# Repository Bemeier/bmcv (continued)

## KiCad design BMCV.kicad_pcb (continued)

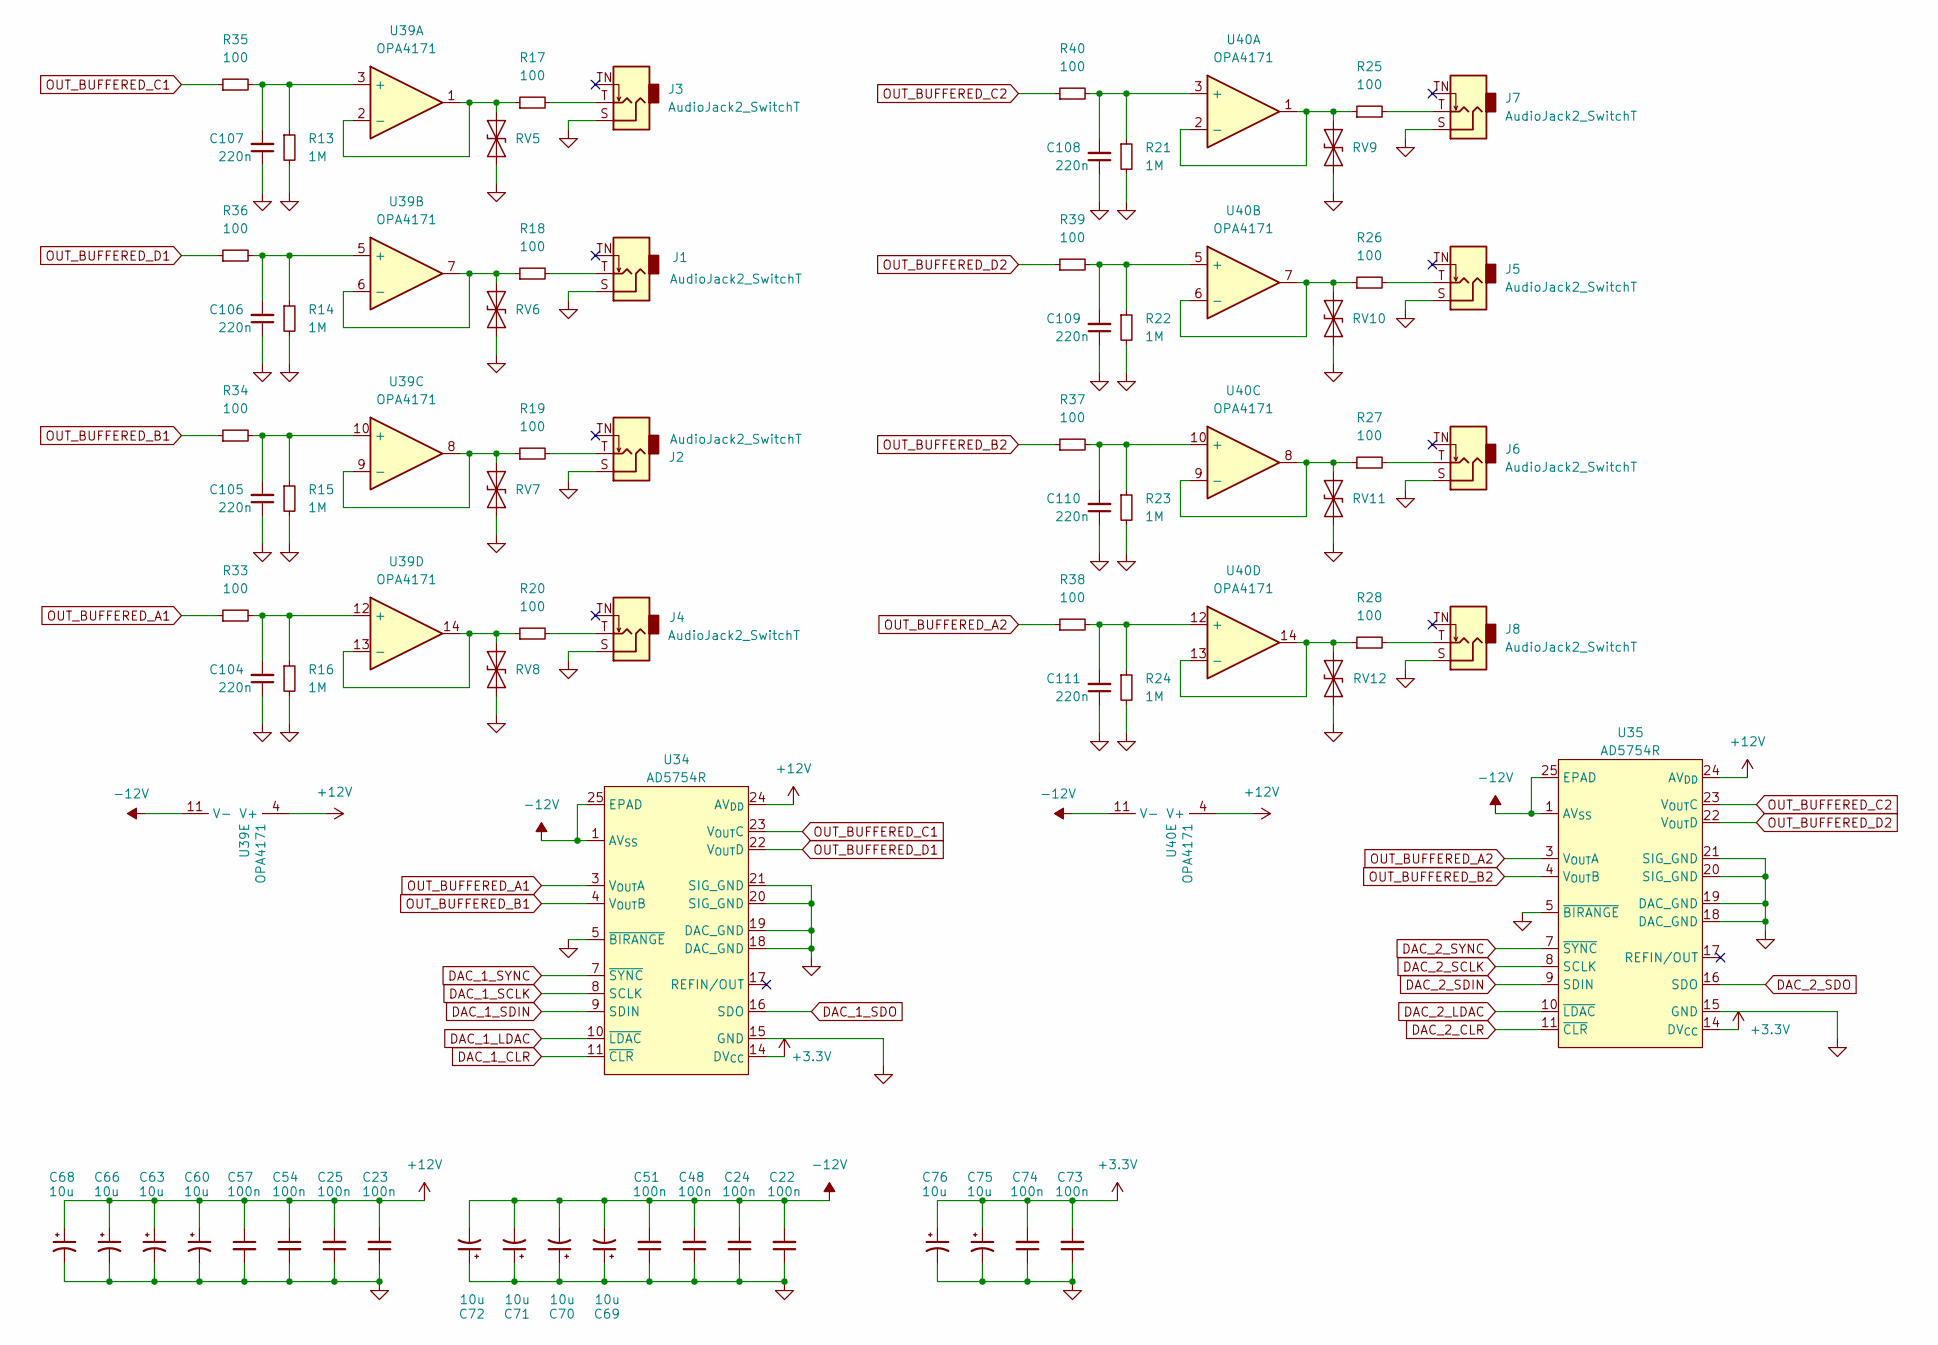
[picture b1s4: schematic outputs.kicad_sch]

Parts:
C22, C23, C24, C25, C48, C51, C54, C57, C73, C74: 100n; C_0603_1608Metric; LCSC Part # C14663
C60, C63, C66, C68, C69, C70, C71, C72, C75, C76: 10u; C_0805_2012Metric; LCSC Part # C237493
C104, C105, C106, C107, C108, C109, C110, C111: 220n; C_0402_1005Metric; LCSC Part # C16772
J1, J2, J3, J4, J5, J6, J7, J8: AudioJack2_SwitchT; Jack_3.5mm_QingPu_WQP-PJ398SM_Vertical_CircularHoles
R13, R14, R15, R16, R21, R22, R23, R24: 1M; R_0603_1608Metric; LCSC Part # C22935
R17, R18, R19, R20, R25, R26, R27, R28: 100; R_0603_1608Metric; LCSC Part # C22775
R33, R34, R35, R36, R37, R38, R39, R40: 100; R_0402_1005Metric; LCSC Part # C25076
RV5, RV6, RV7, RV8, RV9, RV10, RV11, RV12: SD12C-01FTG; D_SOD-323; LCSC Part # C135970
U34, U35: AD5754R; TSSOP-24-1EP_4.4x7.8mm_P0.65mm_EP3.2x5mm; LCSC Part # C392906
U39, U40: OPA4171; TSSOP-14_4.4x5mm_P0.65mm; LCSC Part # C529553

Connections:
3.3V: C73.2, C74.2, C75.1, C76.1, U34.10 (~LDAC), U34.11 (~CLR), U34.14 (DV_{CC}), U35.10 (~LDAC), U35.11 (~CLR), U35.14 (DV_{CC}); also elsewhere on the board
+12V: C23.2, C25.2, C54.1, C57.1, C60.1, C63.1, C66.1, C68.1, U34.24 (AV_{DD}), U35.24 (AV_{DD}), U39.4 (V+), U40.4 (V+); also elsewhere on the board
-12V: C22.2, C24.2, C48.2, C51.2, C69.2, C70.2, C71.2, C72.2, U34.1 (AV_{SS}), U34.25 (EPAD), U35.1 (AV_{SS}), U35.25 (EPAD), U39.11 (V-), U40.11 (V-); also elsewhere on the board
ADC_DAC_SCLK: U34.8 (SCLK), U35.8 (SCLK); also elsewhere on the board
ADC_DAC_SDIN: U34.9 (SDIN); also elsewhere on the board
DAC_1_SYNC: U34.7 (~SYNC), U35.7 (~SYNC); also elsewhere on the board
DAC_2_SDO: U35.16 (SDO)
GND: C22.1, C23.1, C24.1, C25.1, C48.1, C51.1, C54.2, C57.2, C60.2, C63.2, C66.2, C68.2, C69.1, C70.1, C71.1, C72.1, C73.1, C74.1, C75.2, C76.2, C104.1, C105.1, C106.1, C107.1, C108.1, C109.1, C110.1, C111.1, J1.S, J2.S, J3.S, J4.S, J5.S, J6.S, J7.S, J8.S, R13.2, R14.2, R15.2, R16.2, R21.2, R22.2, R23.2, R24.2, RV5.1 (A1), RV6.1 (A1), RV7.1 (A1), RV8.1 (A1), RV9.1 (A1), RV10.1 (A1), RV11.1 (A1), RV12.1 (A1), U34.5 (~BIRANGE), U34.15 (GND), U34.18 (DAC_GND), U34.19 (DAC_GND), U34.20 (SIG_GND), U34.21 (SIG_GND), U35.5 (~BIRANGE), U35.15 (GND), U35.18 (DAC_GND), U35.19 (DAC_GND), U35.20 (SIG_GND), U35.21 (SIG_GND); also elsewhere on the board
unnamed: J1.T, R18.2
unnamed: J2.T, R19.2
unnamed: J3.T, R17.2
unnamed: J4.T, R20.2
unnamed: J5.T, R26.2
unnamed: J6.T, R27.2
unnamed: J7.T, R25.2
unnamed: J8.T, R28.2
unnamed: R17.1, RV5.2 (A2), U39.1, U39.2 (-)
unnamed: R18.1, RV6.2 (A2), U39.6 (-), U39.7
unnamed: R19.1, RV7.2 (A2), U39.8, U39.9 (-)
unnamed: R20.1, RV8.2 (A2), U39.13 (-), U39.14
unnamed: R25.1, RV9.2 (A2), U40.1, U40.2 (-)
unnamed: R26.1, RV10.2 (A2), U40.6 (-), U40.7
unnamed: R27.1, RV11.2 (A2), U40.8, U40.9 (-)
unnamed: R28.1, RV12.2 (A2), U40.13 (-), U40.14
unnamed: C107.2, R13.1, R35.2, U39.3 (+)
unnamed: C106.2, R14.1, R36.2, U39.5 (+)
unnamed: C105.2, R15.1, R34.2, U39.10 (+)
unnamed: C104.2, R16.1, R33.2, U39.12 (+)
unnamed: C108.2, R21.1, R40.2, U40.3 (+)
unnamed: C109.2, R22.1, R39.2, U40.5 (+)
unnamed: C110.2, R23.1, R37.2, U40.10 (+)
unnamed: C111.2, R24.1, R38.2, U40.12 (+)
OUT_BUFFERED_A1: R33.1, U34.3 (V_{OUT}A)
OUT_BUFFERED_A2: R38.1, U35.3 (V_{OUT}A)
OUT_BUFFERED_B1: R34.1, U34.4 (V_{OUT}B)
OUT_BUFFERED_B2: R37.1, U35.4 (V_{OUT}B)
OUT_BUFFERED_C1: R35.1, U34.23 (V_{OUT}C)
OUT_BUFFERED_C2: R40.1, U35.23 (V_{OUT}C)
OUT_BUFFERED_D1: R36.1, U34.22 (V_{OUT}D)
OUT_BUFFERED_D2: R39.1, U35.22 (V_{OUT}D)

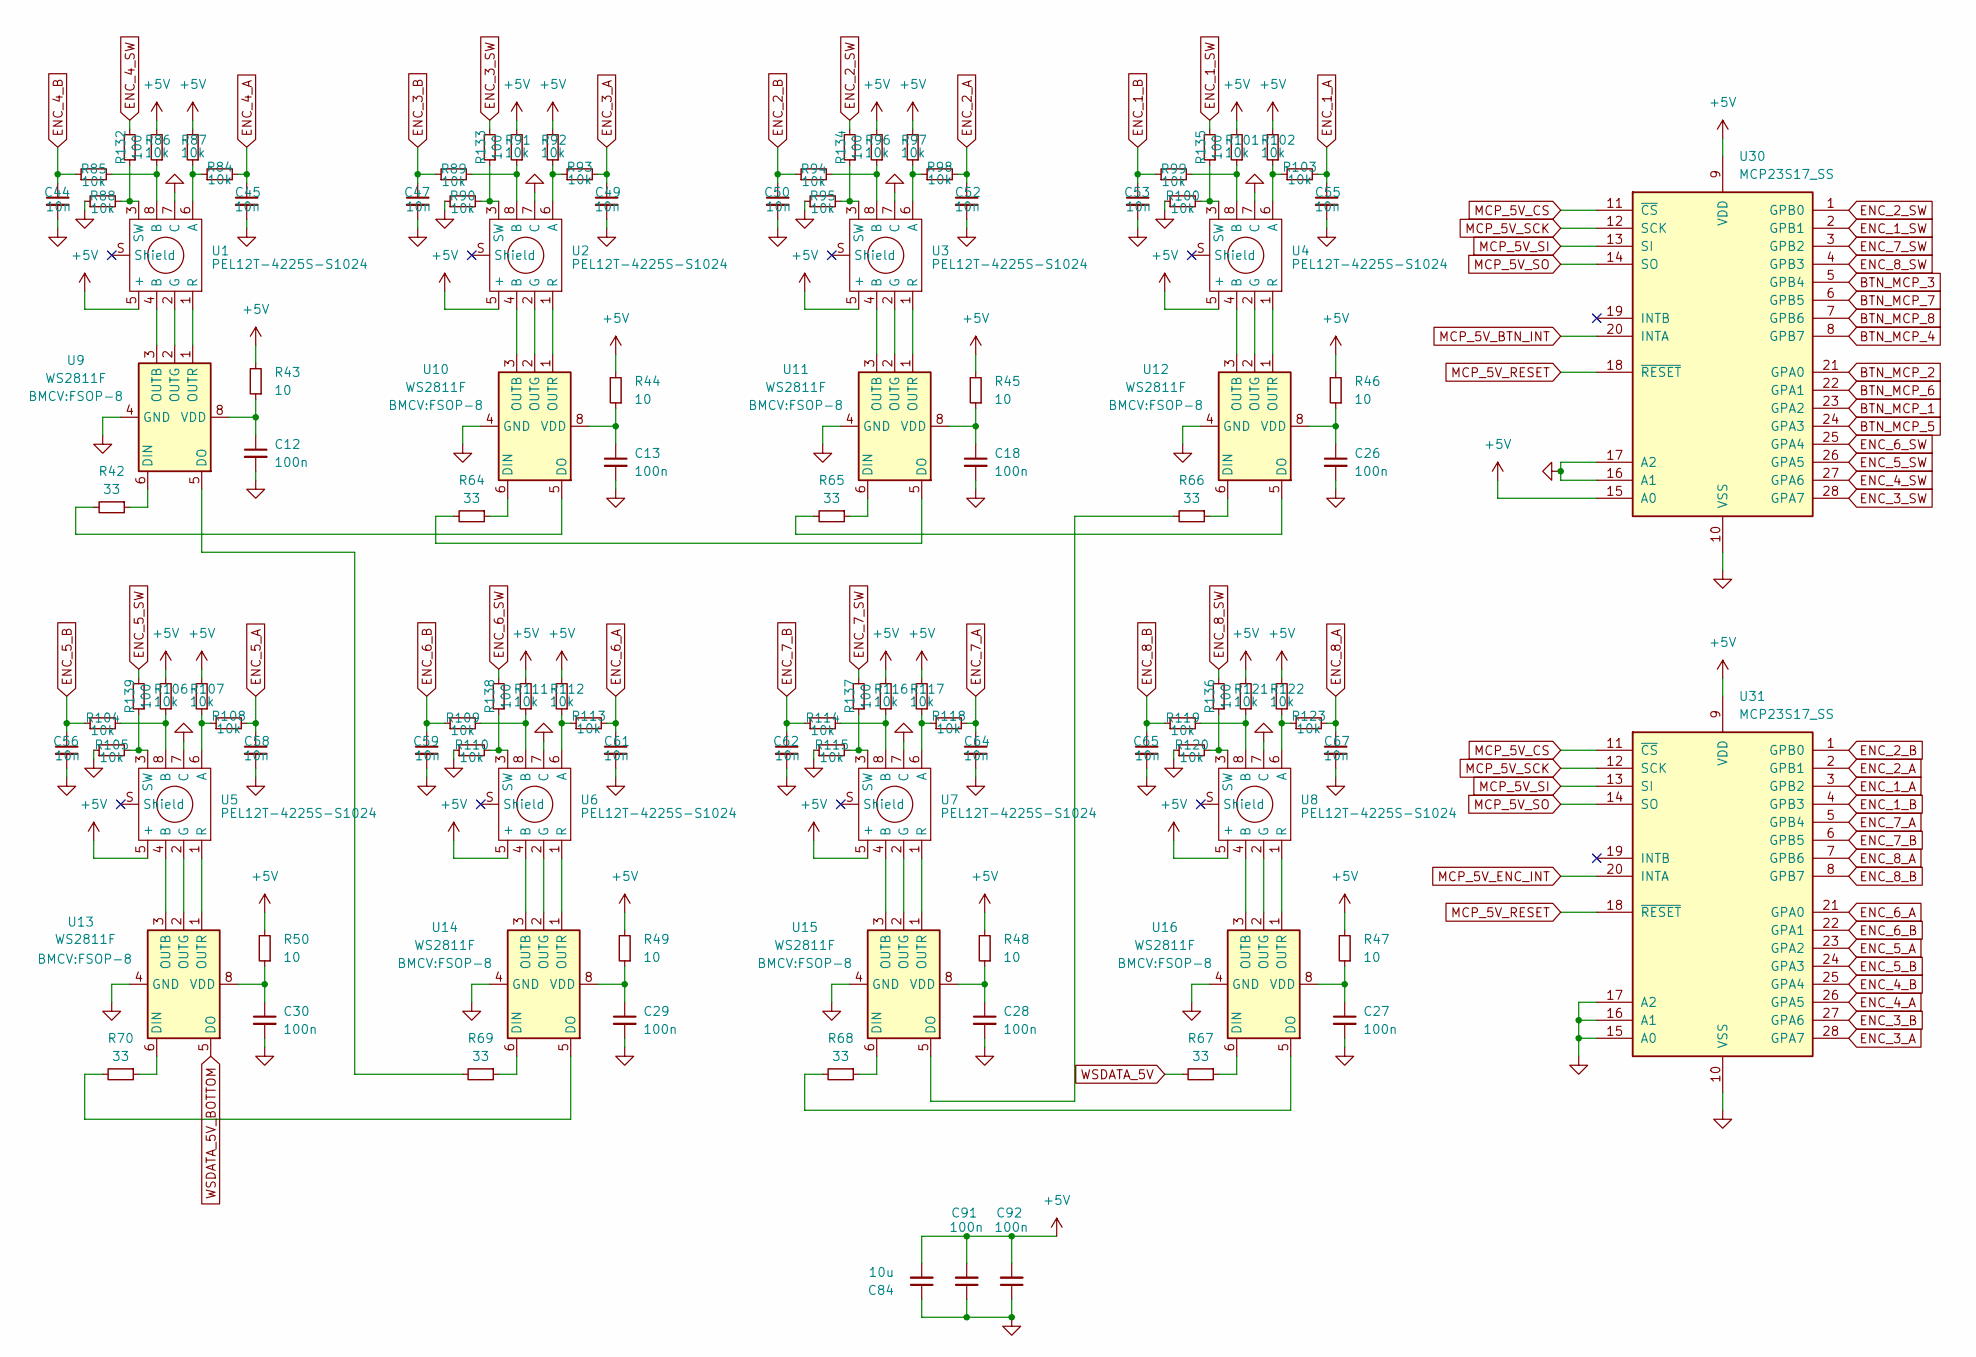
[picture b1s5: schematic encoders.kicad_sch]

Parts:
C12, C13, C18, C26, C27, C28, C29, C30: 100n; C_0402_1005Metric; LCSC Part # C307331
C44, C45, C47, C49, C50, C52, C53, C55, C56, C58, C59, C61, C62, C64, C65, C67: 10n; C_0402_1005Metric; LCSC Part # C15195
C84: 10u; C_0805_2012Metric; LCSC Part # C237493
C91, C92: 100n; C_0603_1608Metric; LCSC Part # C14663
R42, R64, R65, R66, R67, R68, R69, R70: 33; R_0402_1005Metric; LCSC Part # C25105
R43, R44, R45, R46, R47, R48, R49, R50: 10; R_0402_1005Metric; LCSC Part # C25077
R84, R85, R86, R87, R88, R89, R90, R91, R92, R93, R94, R95, R96, R97, R98, R99, R100, R101, R102, R103, R104, R105, R106, R107, R108, R109, R110, R111, R112, R113, R114, R115, R116, R117, R118, R119, R120, R121, R122, R123: 10k; R_0402_1005Metric; LCSC Part # C25744
R132, R133, R134, R135, R136, R137, R138, R139: 100; R_0402_1005Metric; LCSC Part # C25076
U1, U2, U3, U4, U5, U6, U7, U8: PEL12T-4225S-S1024; PEL12T-4xxxS-S1024
U9, U10, U11, U12, U13, U14, U15, U16: WS2811F; FSOP-8; LCSC Part # C5446692
U30, U31: MCP23S17_SS; SSOP-28_5.3x10.2mm_P0.65mm; LCSC Part # C128577

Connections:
+5V: C84.2, C91.2, C92.2, R43.2, R44.2, R45.2, R46.2, R47.2, R48.2, R49.2, R50.2, R86.2, R87.2, R91.2, R92.2, R96.2, R97.2, R101.2, R102.2, R106.2, R107.2, R111.2, R112.2, R116.2, R117.2, R121.2, R122.2, U1.5 (+), U2.5 (+), U3.5 (+), U4.5 (+), U5.5 (+), U6.5 (+), U7.5 (+), U8.5 (+), U30.9 (VDD), U30.15 (A0), U31.9 (VDD); also elsewhere on the board
BTN_MCP_1: U30.23 (GPA2); also elsewhere on the board
BTN_MCP_2: U30.21 (GPA0); also elsewhere on the board
BTN_MCP_3: U30.5 (GPB4); also elsewhere on the board
BTN_MCP_4: U30.8 (GPB7); also elsewhere on the board
BTN_MCP_5: U30.24 (GPA3); also elsewhere on the board
BTN_MCP_6: U30.22 (GPA1); also elsewhere on the board
BTN_MCP_7: U30.6 (GPB5); also elsewhere on the board
BTN_MCP_8: U30.7 (GPB6); also elsewhere on the board
ENC_1_A: C55.1, R103.2, U31.3 (GPB2)
ENC_1_B: C53.1, R99.1, U31.4 (GPB3)
ENC_1_SW: R135.2, U30.2 (GPB1)
ENC_2_A: C52.1, R98.2, U31.2 (GPB1)
ENC_2_B: C50.1, R94.1, U31.1 (GPB0)
ENC_2_SW: R134.2, U30.1 (GPB0)
ENC_3_A: C49.1, R93.2, U31.28 (GPA7)
ENC_3_B: C47.1, R89.1, U31.27 (GPA6)
ENC_3_SW: R133.2, U30.28 (GPA7)
ENC_4_A: C45.1, R84.2, U31.26 (GPA5)
ENC_4_B: C44.1, R85.1, U31.25 (GPA4)
ENC_4_SW: R132.2, U30.27 (GPA6)
ENC_5_A: C58.1, R108.2, U31.23 (GPA2)
ENC_5_B: C56.1, R104.1, U31.24 (GPA3)
ENC_5_SW: R139.2, U30.26 (GPA5)
ENC_6_A: C61.1, R113.2, U31.21 (GPA0)
ENC_6_B: C59.1, R109.1, U31.22 (GPA1)
ENC_6_SW: R138.2, U30.25 (GPA4)
ENC_7_A: C64.1, R118.2, U31.5 (GPB4)
ENC_7_B: C62.1, R114.1, U31.6 (GPB5)
ENC_7_SW: R137.2, U30.3 (GPB2)
ENC_8_A: C67.1, R123.2, U31.7 (GPB6)
ENC_8_B: C65.1, R119.1, U31.8 (GPB7)
ENC_8_SW: R136.2, U30.4 (GPB3)
GND: C12.2, C13.2, C18.2, C26.2, C27.2, C28.2, C29.2, C30.2, C44.2, C45.2, C47.2, C49.2, C50.2, C52.2, C53.2, C55.2, C56.2, C58.2, C59.2, C61.2, C62.2, C64.2, C65.2, C67.2, C84.1, C91.1, C92.1, R88.1, R90.1, R95.1, R100.1, R105.1, R110.1, R115.1, R120.1, U1.7 (C), U2.7 (C), U3.7 (C), U4.7 (C), U5.7 (C), U6.7 (C), U7.7 (C), U8.7 (C), U9.4 (GND), U10.4 (GND), U11.4 (GND), U12.4 (GND), U13.4 (GND), U14.4 (GND), U15.4 (GND), U16.4 (GND), U30.10 (VSS), U30.16 (A1), U30.17 (A2), U31.10 (VSS), U31.15 (A0), U31.16 (A1), U31.17 (A2); also elsewhere on the board
MCP_5V_BTN_INT: U30.20 (INTA); also elsewhere on the board
MCP_5V_CS: U30.11 (~CS), U31.11 (~CS); also elsewhere on the board
MCP_5V_ENC_INT: U31.20 (INTA); also elsewhere on the board
MCP_5V_RESET: U30.18 (~RESET), U31.18 (~RESET); also elsewhere on the board
MCP_5V_SCK: U30.12 (SCK), U31.12 (SCK); also elsewhere on the board
MCP_5V_SI: U30.13 (SI), U31.13 (SI); also elsewhere on the board
MCP_5V_SO: U30.14 (SO), U31.14 (SO); also elsewhere on the board
unnamed: R85.2, R86.1, U1.8 (B)
unnamed: R89.2, R91.1, U2.8 (B)
unnamed: R94.2, R96.1, U3.8 (B)
unnamed: R99.2, R101.1, U4.8 (B)
unnamed: R104.2, R106.1, U5.8 (B)
unnamed: R109.2, R111.1, U6.8 (B)
unnamed: R114.2, R116.1, U7.8 (B)
unnamed: R119.2, R121.1, U8.8 (B)
unnamed: R84.1, R87.1, U1.6 (A)
unnamed: U1.2 (G), U9.2 (OUTG)
unnamed: U1.1 (R), U9.1 (OUTR)
unnamed: R88.2, R132.1, U1.3 (SW)
unnamed: R92.1, R93.1, U2.6 (A)
unnamed: R90.2, R133.1, U2.3 (SW)
unnamed: R97.1, R98.1, U3.6 (A)
unnamed: R95.2, R134.1, U3.3 (SW)
unnamed: R102.1, R103.1, U4.6 (A)
unnamed: R100.2, R135.1, U4.3 (SW)
unnamed: R107.1, R108.1, U5.6 (A)
unnamed: R105.2, R139.1, U5.3 (SW)
unnamed: R112.1, R113.1, U6.6 (A)
unnamed: R110.2, R138.1, U6.3 (SW)
unnamed: R117.1, R118.1, U7.6 (A)
unnamed: R115.2, R137.1, U7.3 (SW)
unnamed: R122.1, R123.1, U8.6 (A)
unnamed: R120.2, R136.1, U8.3 (SW)
unnamed: R42.1, U9.6 (DIN)
unnamed: R69.2, U9.5 (DO)
unnamed: U1.4 (B), U9.3 (OUTB)
unnamed: C12.1, R43.1, U9.8 (VDD)
unnamed: R64.1, U10.6 (DIN)
unnamed: R42.2, U10.5 (DO)
unnamed: U2.4 (B), U10.3 (OUTB)
unnamed: U2.2 (G), U10.2 (OUTG)
unnamed: U2.1 (R), U10.1 (OUTR)
unnamed: C13.1, R44.1, U10.8 (VDD)
unnamed: R65.1, U11.6 (DIN)
unnamed: R64.2, U11.5 (DO)
unnamed: U3.4 (B), U11.3 (OUTB)
unnamed: U3.2 (G), U11.2 (OUTG)
unnamed: U3.1 (R), U11.1 (OUTR)
unnamed: C18.1, R45.1, U11.8 (VDD)
unnamed: R66.1, U12.6 (DIN)
unnamed: R65.2, U12.5 (DO)
unnamed: U4.4 (B), U12.3 (OUTB)
unnamed: U4.2 (G), U12.2 (OUTG)
unnamed: U4.1 (R), U12.1 (OUTR)
unnamed: C26.1, R46.1, U12.8 (VDD)
unnamed: R70.1, U13.6 (DIN)
unnamed: U5.4 (B), U13.3 (OUTB)
unnamed: U5.2 (G), U13.2 (OUTG)
unnamed: U5.1 (R), U13.1 (OUTR)
unnamed: C30.1, R50.1, U13.8 (VDD)
unnamed: R69.1, U14.6 (DIN)
unnamed: R70.2, U14.5 (DO)
unnamed: U6.4 (B), U14.3 (OUTB)
unnamed: U6.2 (G), U14.2 (OUTG)
unnamed: U6.1 (R), U14.1 (OUTR)
unnamed: C29.1, R49.1, U14.8 (VDD)
unnamed: R68.1, U15.6 (DIN)
unnamed: R66.2, U15.5 (DO)
unnamed: U7.4 (B), U15.3 (OUTB)
unnamed: U7.2 (G), U15.2 (OUTG)
unnamed: U7.1 (R), U15.1 (OUTR)
unnamed: C28.1, R48.1, U15.8 (VDD)
unnamed: R67.1, U16.6 (DIN)
unnamed: R68.2, U16.5 (DO)
unnamed: U8.4 (B), U16.3 (OUTB)
unnamed: U8.2 (G), U16.2 (OUTG)
unnamed: U8.1 (R), U16.1 (OUTR)
unnamed: C27.1, R47.1, U16.8 (VDD)
WSDATA_5V: R67.2; also elsewhere on the board
WSDATA_5V_BOTTOM: U13.5 (DO); also elsewhere on the board

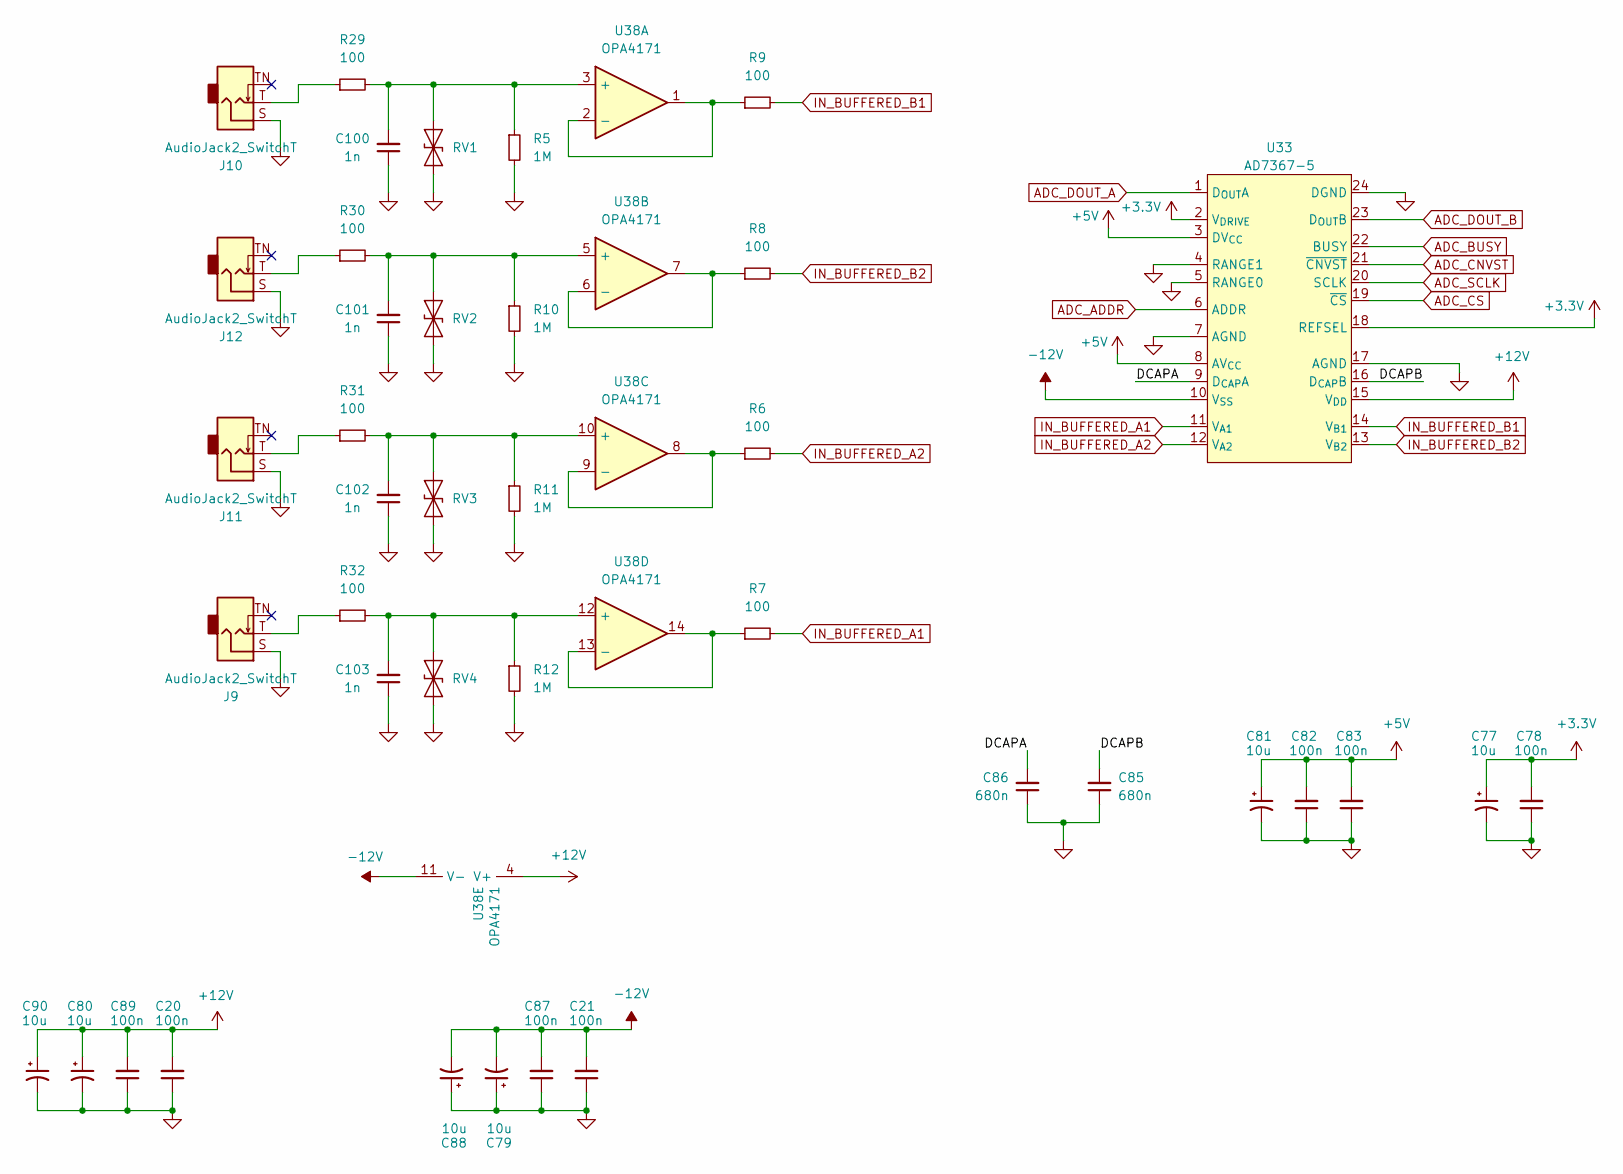
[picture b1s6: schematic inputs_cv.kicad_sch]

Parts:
C20, C21, C87, C89: 100n; C_0603_1608Metric; LCSC Part # C14663
C77, C79, C80, C81, C88, C90: 10u; C_0805_2012Metric; LCSC Part # C237493
C78, C82, C83: 100n; C_0402_1005Metric; LCSC Part # C307331
C85, C86: 680n; C_0603_1608Metric; LCSC Part # C5143539
C100, C101, C102, C103: 1n; C_0402_1005Metric; LCSC Part # C1523
J9, J10, J11, J12: AudioJack2_SwitchT; Jack_3.5mm_QingPu_WQP-PJ398SM_Vertical_CircularHoles
R5, R10, R11, R12: 1M; R_0603_1608Metric; LCSC Part # C22935
R6, R7, R8, R9: 100; R_0402_1005Metric; LCSC Part # C25076
R29, R30, R31, R32: 100; R_0603_1608Metric; LCSC Part # C22775
RV1, RV2, RV3, RV4: SD12C-01FTG; D_SOD-323; LCSC Part # C135970
U33: AD7367-5; TSSOP-24_4.4x7.8mm_P0.65mm; LCSC Part # C650862
U38: OPA4171; TSSOP-14_4.4x5mm_P0.65mm; LCSC Part # C529553

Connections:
3.3V: C77.1, C78.2, U33.2 (V_{DRIVE}), U33.18 (REFSEL); also elsewhere on the board
+5V: C81.1, C82.2, C83.2, U33.3 (DV_{CC}), U33.8 (AV_{CC}); also elsewhere on the board
+12V: C20.2, C80.1, C89.2, C90.1, U33.15 (V_{DD}), U38.4 (V+); also elsewhere on the board
-12V: C21.2, C79.2, C87.2, C88.2, U33.10 (V_{SS}), U38.11 (V-); also elsewhere on the board
/InputsCV/DCAPA: C86.2, U33.9 (D_{CAP}A)
/InputsCV/DCAPB: C85.2, U33.16 (D_{CAP}B)
ADC_ADDR: U33.6 (ADDR); also elsewhere on the board
ADC_BUSY: U33.22 (BUSY); also elsewhere on the board
ADC_CNVST: U33.21 (~CNVST); also elsewhere on the board
ADC_CS: U33.19 (~CS); also elsewhere on the board
ADC_DAC_SCLK: U33.20 (SCLK); also elsewhere on the board
ADC_DAC_SDO: U33.1 (D_{OUT}A); also elsewhere on the board
ADC_DOUT_B: U33.23 (D_{OUT}B)
GND: C20.1, C21.1, C77.2, C78.1, C79.1, C80.2, C81.2, C82.1, C83.1, C85.1, C86.1, C87.1, C88.1, C89.1, C90.2, C100.1, C101.1, C102.1, C103.1, J9.S, J10.S, J11.S, J12.S, R5.2, R10.2, R11.2, R12.2, RV1.1 (A1), RV2.1 (A1), RV3.1 (A1), RV4.1 (A1), U33.4 (RANGE1), U33.5 (RANGE0), U33.7 (AGND), U33.17 (AGND), U33.24 (DGND); also elsewhere on the board
IN_BUFFERED_A1: R7.2, U33.11 (V_{A1})
IN_BUFFERED_A2: R6.2, U33.12 (V_{A2})
IN_BUFFERED_B1: R9.2, U33.14 (V_{B1})
IN_BUFFERED_B2: R8.2, U33.13 (V_{B2})
unnamed: J9.T, R32.1
unnamed: J10.T, R29.1
unnamed: J11.T, R31.1
unnamed: J12.T, R30.1
unnamed: C100.2, R5.1, R29.2, RV1.2 (A2), U38.3 (+)
unnamed: C101.2, R10.1, R30.2, RV2.2 (A2), U38.5 (+)
unnamed: C102.2, R11.1, R31.2, RV3.2 (A2), U38.10 (+)
unnamed: C103.2, R12.1, R32.2, RV4.2 (A2), U38.12 (+)
unnamed: R9.1, U38.1, U38.2 (-)
unnamed: R8.1, U38.6 (-), U38.7
unnamed: R6.1, U38.8, U38.9 (-)
unnamed: R7.1, U38.13 (-), U38.14

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
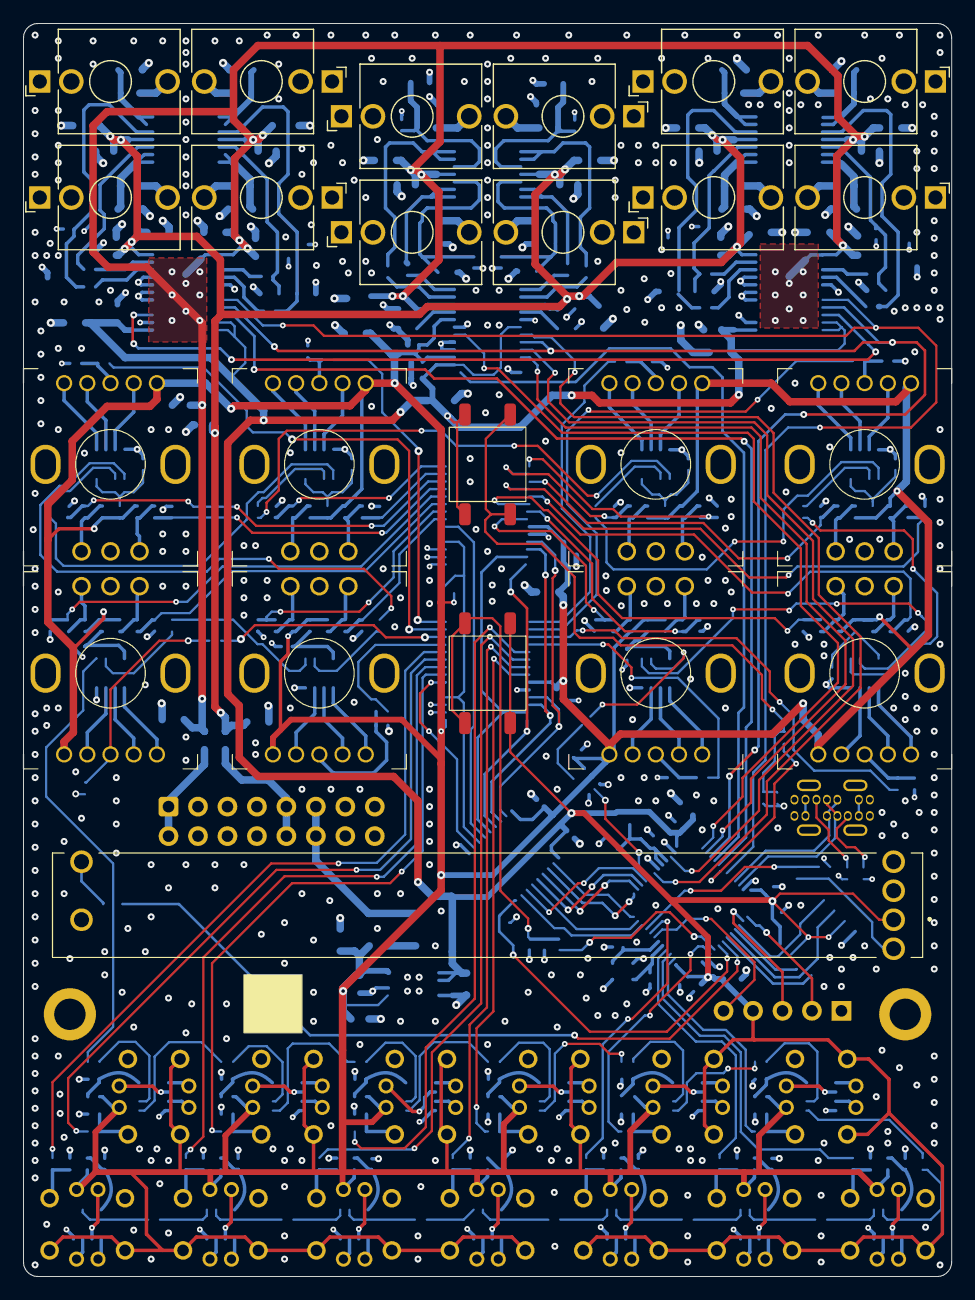
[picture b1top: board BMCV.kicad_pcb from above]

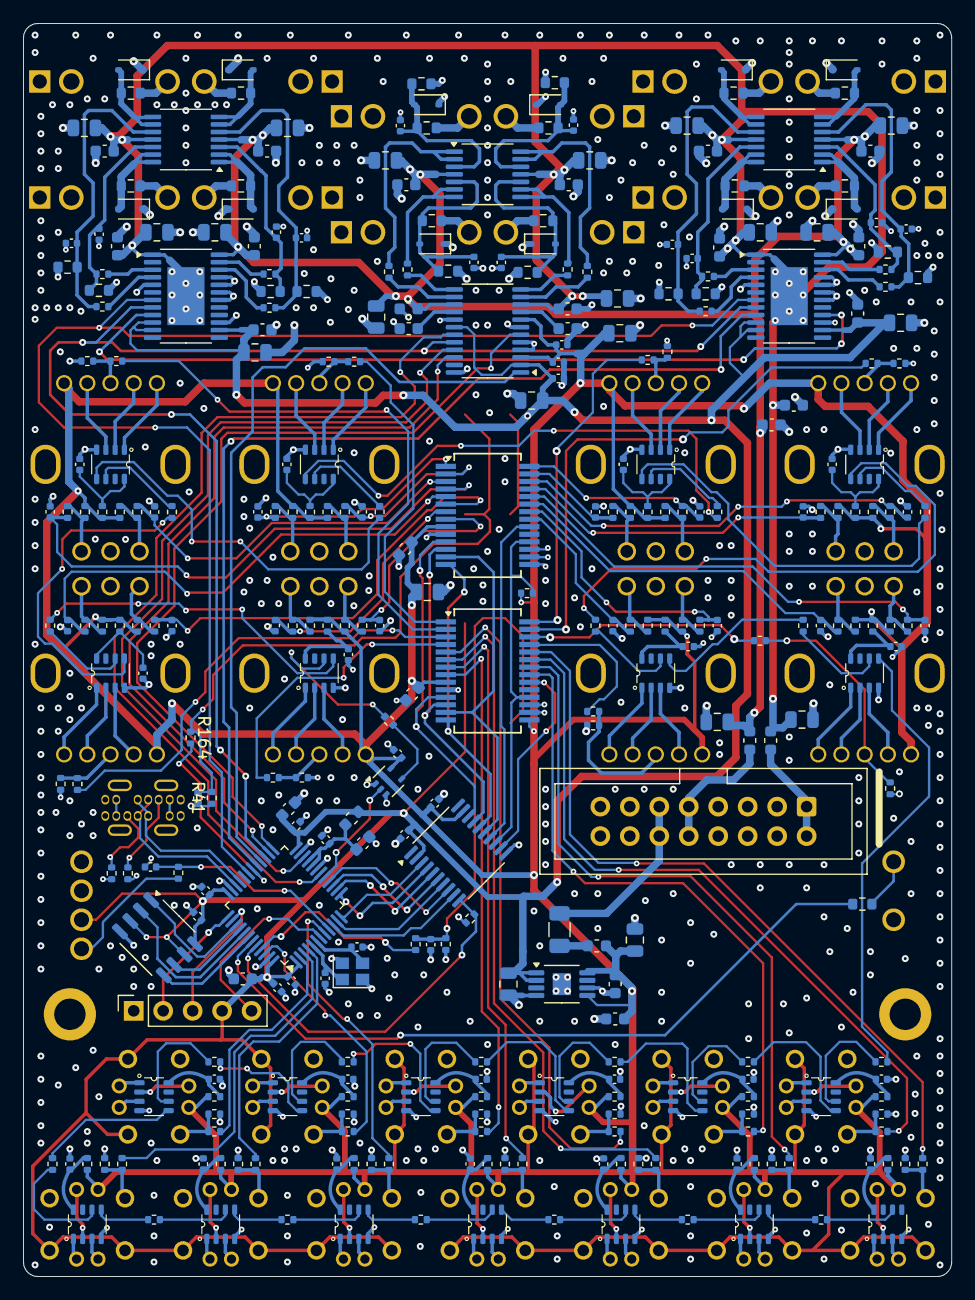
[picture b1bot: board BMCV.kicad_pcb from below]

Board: 4 copper layers, 80.0 x 108.0 mm, 366 parts (328 on the bottom side), 307 nets.

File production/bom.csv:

Designator,Footprint,Quantity,Value,LCSC Part #
"C1, C2",0402,2,10p,C161520
"C10, C16, C7, C9",0603,4,1u,C15849
"C11, C12, C13, C18, C26, C27, C28, C29, C3, C30, C31, C32, C33, C34, C35, C36, C37, C38, C39, C4, C40, C41, C42, C43, C46, C5, C6, C78, C82, C83, C93, C94, C95, C99",0402,34,100n,C307331
"C14, C17, C19, C20, C21, C22, C23, C24, C25, C48, C51, C54, C57, C73, C74, C87, C89, C91, C92",0603,19,100n,C14663
"C15, C97, C98",0805,3,22u,C45783
"C44, C45, C47, C49, C50, C52, C53, C55, C56, C58, C59, C61, C62, C64, C65, C67, C8",0402,17,10n,C15195
"C60, C63, C66, C68, C69, C70, C71, C72, C75, C76, C77, C79, C80, C81, C84, C88, C90, C96",0805,18,10u,C237493
"C85, C86",0603,2,680nF,C5143539
F1,1206,1,SMD1206P110TF,C20801
"FB1, FB2, FB3, FB4",0603,4,470R,C114780
"J1, J10, J11, J12, J2, J3, J4, J5, J6, J7, J8, J9",Jack_3.5mm_QingPu_WQP-PJ398SM_Vertical_CircularHoles,12,AudioJack2_SwitchT,
J14,GT-USB-7035E,1,USB_C_Receptacle_USB2.0_14P,C22384784
"R1, R158, R2, R3",0402,4,5k1,C25905
"R10, R11, R12, R13, R14, R15, R16, R21, R22, R23, R24, R5",0603,12,10M,C7250
"R100, R101, R102, R103, R104, R105, R106, R107, R108, R109, R110, R111, R112, R113, R114, R115, R116, R117, R118, R119, R120, R121, R122, R123, R124, R125, R126, R127, R128, R129, R130, R131, R149, R151, R153, R155, R157, R159, R161, R162, R84, R85, R86, R87, R88, R89, R90, R91, R92, R93, R94, R95, R96, R97, R98, R99",0402,56,10k,C25744
"R132, R133, R134, R135, R136, R137, R138, R139, R140, R141, R142, R143, R144, R145, R146, R147, R148, R150, R152, R154, R156, R163, R33, R34, R35, R36, R37, R38, R39, R40, R6, R7, R8, R9",0402,34,100,C25076
"R17, R18, R19, R20, R25, R26, R27, R28, R29, R30, R31, R32",0603,12,100,C22775
R4,0603,1,1k5,C22843
"R42, R64, R65, R66, R67, R68, R69, R70, R71, R72, R73, R74, R75, R76, R77, R78, R79, R80, R81, R82, R83",0402,21,33,C25105
"R43, R44, R45, R46, R47, R48, R49, R50, R51, R52, R53, R54, R55, R56, R57, R58, R59, R60, R61, R62, R63",0402,21,10,C25077
"RV1, RV10, RV11, RV12, RV2, RV3, RV4, RV5, RV6, RV7, RV8, RV9",D_SOD-323,12,SD12C-01FTG,C135970
"SW1, SW10, SW11, SW12, SW13, SW2, SW3, SW4, SW5, SW6, SW7, SW8, SW9",TC002-N11AXXX-RGB,13,TC002-N11AS2XT-RGB,
SW14,TS-1095PS-AXXBX-C3DX,1,Reset,C2834959
SW15,TS-1095PS-AXXBX-C3DX,1,Boot,C2834959
"U1, U2, U3, U4, U5, U6, U7, U8",PEL12T-4xxxS-S1024,8,PEL12T-4225S-S1024,
"U10, U11, U12, U13, U14, U15, U16, U17, U18, U19, U20, U21, U22, U23, U24, U25, U26, U27, U28, U29, U9",FSOP-8,21,WS2811F,C5446692
"U30, U31",SSOP-28_5.3x10.2mm_P0.65mm,2,MCP23S17_SS,C128577
U32,TSSOP-20_4.4x6.5mm_P0.65mm,1,TXS0108EPW,C17206
U33,TSSOP-24_4.4x7.8mm_P0.65mm,1,AD7367-5,C650862
"U34, U35",TSSOP-24-1EP_4.4x7.8mm_P0.65mm_EP3.2x5mm,2,AD5754R,C392906
U36,LQFP-48_7x7mm_P0.5mm,1,STM32G474CETx,C730125
U37,SSOP-8_3.9x5.05mm_P1.27mm,1,MB85RS64PNF-G-JNERE1,C8741
"U38, U39, U40",TSSOP-14_4.4x5mm_P0.65mm,3,OPA4171,C529553
U41,HVSSOP-8-1EP_3x3mm_P0.65mm_EP1.57x1.89mm,1,TLV76733,C2873382
VR1,PTL6015xxxxxxx,1,PTL60-15G1-103B2,
Y1,Crystal_SMD_2520-4Pin_2.5x2.0mm,1,38.4MHz 10pF,C3020671

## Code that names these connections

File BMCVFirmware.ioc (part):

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Mcu.Name=STM32G474C(B-C-E)Tx
Mcu.Package=LQFP48
Mcu.UserName=STM32G474CETx
PA0.GPIOParameters=GPIO_Label
PA0.GPIO_Label=IN_BTN_MCU3
PA0.Signal=GPIO_Input
PA1.GPIOParameters=GPIO_Label
PA1.GPIO_Label=ADC1_IN2_SLIDER
PA1.Mode=IN2-Single-Ended
PA1.Signal=ADC1_IN2
PA10.GPIOParameters=GPIO_Speed,PinState,GPIO_Label
PA10.GPIO_Label=OUT_DAC_SYNC
PA10.GPIO_Speed=GPIO_SPEED_FREQ_HIGH
PA10.PinState=GPIO_PIN_SET
PA10.Signal=GPIO_Output
PA11.Mode=Device
PA11.Signal=USB_DM
PA12.Mode=Device
PA12.Signal=USB_DP
PA13.Mode=Serial_Wire
PA13.Signal=SYS_JTMS-SWDIO
PA14.Mode=Serial_Wire
PA14.Signal=SYS_JTCK-SWCLK
PA15.GPIOParameters=GPIO_Speed,GPIO_Label
PA15.GPIO_Label=SPI3_FRAM_CS
PA15.GPIO_Speed=GPIO_SPEED_FREQ_HIGH
PA15.Signal=GPIO_Output
PA2.GPIOParameters=GPIO_Label
PA2.GPIO_Label=INT_MCP_BTN
PA2.Signal=GPXTI2
PA3.GPIOParameters=GPIO_Label
PA3.GPIO_Label=INT_MCP_ENC
PA3.Signal=GPXTI3
PA4.GPIOParameters=GPIO_Speed,GPIO_Label
PA4.GPIO_Label=OUT_MCP_CS
PA4.GPIO_Speed=GPIO_SPEED_FREQ_HIGH
PA4.Signal=GPIO_Output
PA5.GPIOParameters=GPIO_Speed,GPIO_Label
PA5.GPIO_Label=SPI1_MCP_SCK
PA5.GPIO_Speed=GPIO_SPEED_FREQ_HIGH
PA5.Mode=Full_Duplex_Master
PA5.Signal=SPI1_SCK
PA6.GPIOParameters=GPIO_Speed,GPIO_Label
PA6.GPIO_Label=SPI1_MCP_MISO
PA6.GPIO_Speed=GPIO_SPEED_FREQ_HIGH
PA6.Mode=Full_Duplex_Master
PA6.Signal=SPI1_MISO
PA7.GPIOParameters=GPIO_Speed,GPIO_Label
PA7.GPIO_Label=SPI1_MCP_MOSI
PA7.GPIO_Speed=GPIO_SPEED_FREQ_HIGH
PA7.Mode=Full_Duplex_Master
PA7.Signal=SPI1_MOSI
PA8.GPIOParameters=GPIO_Label
PA8.GPIO_Label=MENU_BTN_2
PA8.Signal=GPIO_Input
PA9.GPIOParameters=GPIO_Speed,PinState,GPIO_Label
PA9.GPIO_Label=EXTRA_PA9
PA9.GPIO_Speed=GPIO_SPEED_FREQ_HIGH
PA9.PinState=GPIO_PIN_SET
PA9.Signal=GPIO_Output
PB0.GPIOParameters=GPIO_Speed,GPIO_Label
PB0.GPIO_Label=OUT_MCP_RESET
PB0.GPIO_Speed=GPIO_SPEED_FREQ_HIGH
PB0.Signal=GPIO_Output
PB1.GPIOParameters=GPIO_Speed,GPIO_Label
PB1.GPIO_Label=WS_TIM3_CH4
PB1.GPIO_Speed=GPIO_SPEED_FREQ_LOW
PB1.Signal=S_TIM3_CH4
PB10.GPIOParameters=GPIO_Speed,PinState,GPIO_Label
PB10.GPIO_Label=OUT_ADC_CNVST
PB10.GPIO_Speed=GPIO_SPEED_FREQ_HIGH
PB10.PinState=GPIO_PIN_SET
PB10.Signal=GPIO_Output
PB11.GPIOParameters=GPIO_Speed,PinState,GPIO_Label
PB11.GPIO_Label=OUT_ADC_ADDR
PB11.GPIO_Speed=GPIO_SPEED_FREQ_HIGH
PB11.PinState=GPIO_PIN_RESET
PB11.Signal=GPIO_Output
PB12.GPIOParameters=GPIO_Label,GPIO_ModeDefaultEXTI
PB12.GPIO_Label=INT_ADC_BUSY
PB12.GPIO_ModeDefaultEXTI=GPIO_MODE_IT_FALLING
PB12.Signal=GPXTI12
PB13.GPIOParameters=GPIO_Speed,GPIO_Label
PB13.GPIO_Label=SPI2_DAC_ADC_SCK
PB13.GPIO_Speed=GPIO_SPEED_FREQ_HIGH
PB13.Mode=Full_Duplex_Master
PB13.Signal=SPI2_SCK
PB14.GPIOParameters=GPIO_Speed,GPIO_Label
PB14.GPIO_Label=SPI2_DAC_ADC_MISO
PB14.GPIO_Speed=GPIO_SPEED_FREQ_HIGH
PB14.Mode=Full_Duplex_Master
PB14.Signal=SPI2_MISO
PB15.GPIOParameters=GPIO_Speed,GPIO_Label
PB15.GPIO_Label=SPI2_DAC_ADC_MOSI
PB15.GPIO_Speed=GPIO_SPEED_FREQ_HIGH
PB15.Mode=Full_Duplex_Master
PB15.Signal=SPI2_MOSI
PB2.GPIOParameters=GPIO_Speed,PinState,GPIO_Label
PB2.GPIO_Label=OUT_ADC_CS
PB2.GPIO_Speed=GPIO_SPEED_FREQ_HIGH
PB2.PinState=GPIO_PIN_SET
PB2.Signal=GPIO_Output
PB3.GPIOParameters=GPIO_Speed,GPIO_Label
PB3.GPIO_Label=SPI3_FRAM_SCK
PB3.GPIO_Speed=GPIO_SPEED_FREQ_HIGH
PB3.Mode=Full_Duplex_Master
PB3.Signal=SPI3_SCK
PB4.GPIOParameters=GPIO_Speed,GPIO_Label
PB4.GPIO_Label=SPI3_FRAM_MISO
PB4.GPIO_Speed=GPIO_SPEED_FREQ_HIGH
PB4.Mode=Full_Duplex_Master
PB4.Signal=SPI3_MISO
PB5.GPIOParameters=GPIO_Speed,GPIO_Label
PB5.GPIO_Label=SPI3_FRAM_MOSI
PB5.GPIO_Speed=GPIO_SPEED_FREQ_HIGH
PB5.Mode=Full_Duplex_Master
PB5.Signal=SPI3_MOSI
PB6.GPIOParameters=GPIO_Label
PB6.GPIO_Label=MENU_BTN_3
PB6.Signal=GPIO_Input
PB7.GPIOParameters=GPIO_Label
PB7.GPIO_Label=LEVEL_SHIFTER_EN
PB7.Signal=GPIO_Output
PB8-BOOT0.GPIOParameters=GPIO_Label
PB8-BOOT0.GPIO_Label=MENU_BTN_BOOT
PB8-BOOT0.Signal=GPIO_Input
PB9.GPIOParameters=GPIO_Label
PB9.GPIO_Label=IN_BTN_MCU1
PB9.Signal=GPIO_Input
PC13.GPIOParameters=GPIO_Label
PC13.GPIO_Label=IN_BTN_MCU2
PC13.Signal=GPIO_Input
PC14-OSC32_IN.GPIOParameters=GPIO_Label
PC14-OSC32_IN.GPIO_Label=IN_BTN_MCU5
PC14-OSC32_IN.Signal=GPIO_Input
PC15-OSC32_OUT.GPIOParameters=GPIO_Label
PC15-OSC32_OUT.GPIO_Label=IN_BTN_MCU4
PC15-OSC32_OUT.Signal=GPIO_Input
PF0-OSC_IN.Mode=HSE-External-Oscillator
PF0-OSC_IN.Signal=RCC_OSC_IN
PF1-OSC_OUT.Mode=HSE-External-Oscillator
PF1-OSC_OUT.Signal=RCC_OSC_OUT
RCC.HSE_VALUE=38400000
RCC.SYSCLKFreq_VALUE=144000000
RCC.SYSCLKSource=RCC_SYSCLKSOURCE_PLLCLK
board=custom

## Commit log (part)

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2025-01-04 rename symbol & footprint libs
2025-01-04 add gitignore, readme & license
2025-01-04 fix extension
2025-01-05 clea up project
2025-01-05 Routing WIP
2025-01-12 routing progress (bottom buttons & encoders)
2025-01-12 remove expander for now, update model/move usb
2025-01-26 switches & led data routing
2025-02-16 completed routing and mcu pins
2025-02-16 applied rules to project
2025-02-16 add img
2025-02-16 update render url
2025-02-23 cleanup
2025-02-23 alpha
2025-02-23 add logo
2025-02-23 fix & add bom
2025-03-21 first ordered verrsion
2025-03-22 kicad v9
2025-04-06 fix ws-2811 footprint
2025-04-14 add test firwmware
2025-04-14 testing dac
2025-04-14 dac working
2025-04-14 debug
2025-04-16 all working
2025-04-18 led test
2025-04-18 pcb changes
2025-04-18 RC filters on DAC output
2025-04-18 slider
2025-04-18 test fram
2025-04-22 test
2025-04-22 soft cs
2025-04-22 pcb routing
2025-04-22 factor out mcp code
2025-04-22 migrate dac adc
2025-04-23 stuff
2025-04-23 firmware
2025-04-27 update footprint slightly to possibly support 228C series LED Switches
2025-04-27 envelope test
2025-04-27 pcb update
2025-04-27 vscode / cmake setup
2025-06-07 setup
2025-06-07 refactor
2025-06-07 fix boot button
2025-08-01 clean up project setup
2025-08-01 rename folder
2025-08-02 update project
2025-08-02 project cleanup
2025-08-23 scenes, quantizer
2025-08-24 clock tracking
2025-08-24 fixed phase error term
2025-12-14 monitor inputs, refactor
2025-12-15 remove lat point, basic input assign
2025-12-16 quantize states
2025-12-16 Refactor state
2025-12-16 wip store/save/copy/clear
2025-12-16 copy/clear/store/load
2025-12-23 untested
2026-05-17 input add/mult
2026-05-18 readme & performance
2026-05-24 Update project structure
2026-05-31 Formatting code
2026-05-31 clang fix
2026-05-31 update setup
